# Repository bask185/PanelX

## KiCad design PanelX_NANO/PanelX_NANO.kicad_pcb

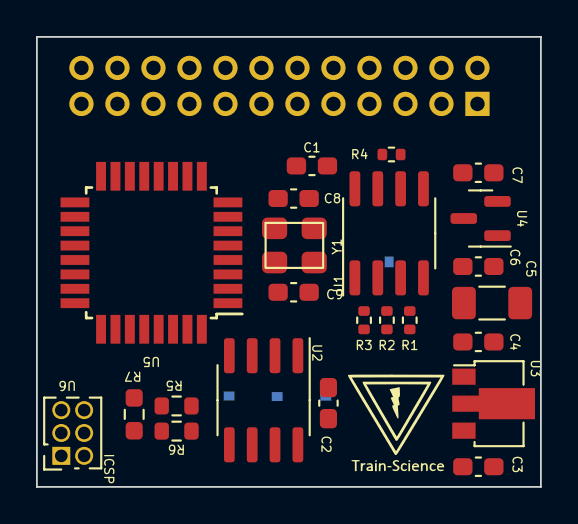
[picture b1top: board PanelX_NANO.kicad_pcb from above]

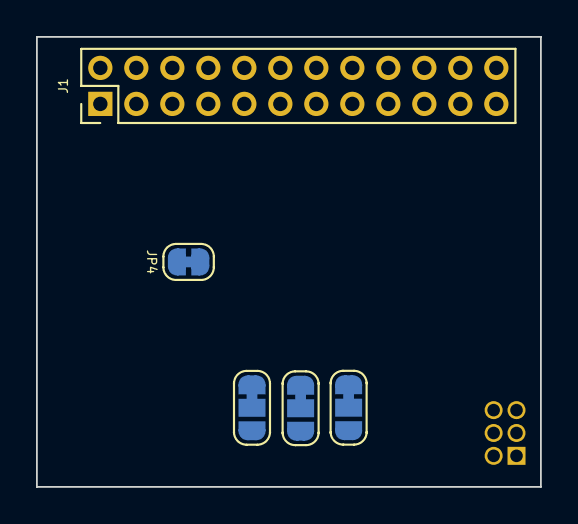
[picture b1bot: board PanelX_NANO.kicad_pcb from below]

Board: 2 copper layers, 28.0 x 25.0 mm, 28 parts (5 on the bottom side), 33 nets, no tracks yet.

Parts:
C1: 100n; C_0603_1608Metric_Pad1.08x0.95mm_HandSolder
C2, C4: 100nF; C_0603_1608Metric_Pad1.08x0.95mm_HandSolder
C3: 330nF; C_0603_1608Metric_Pad1.08x0.95mm_HandSolder
C5: 100uF; C_1206_3216Metric_Pad1.33x1.80mm_HandSolder
C6, C7: 1uF; C_0603_1608Metric_Pad1.08x0.95mm_HandSolder
C8, C9: 12pF; C_0603_1608Metric_Pad1.08x0.95mm_HandSolder
J1: Conn_02x12_Counter_Clockwise; PinHeader_2x12_P2.00mm_Vertical
JP1, JP2, JP3: SolderJumper_3_Bridged12; SolderJumper-3_P1.3mm_Bridged12_RoundedPad1.0x1.5mm_NumberL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
JP4: SolderJumper_2_Bridged; SolderJumper-2_P1.3mm_Bridged_RoundedPad1.0x1.5mm
R1, R2, R3: 10k; R_0402_1005Metric
R4: 120R; R_0402_1005Metric
R5, R6: 4k7; R_0603_1608Metric
R7: 10k; R_0603_1608Metric_Pad0.98x0.95mm_HandSolder
U1: MAX485E; SOIC-8_3.9x4.9mm_P1.27mm
U2: 24LC256; SOIC-8_3.9x4.9mm_P1.27mm
U3: L78L05_SOT89; SOT-89-3
U4: XC6206PxxxMR; SOT-23
U5: ATmega328-A; TQFP-32_7x7mm_P0.8mm
U6: HEADER_3x2; PinSocket_2x03_P1.27mm_Vertical
Y1: crystal_arduino

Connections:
+3V3: C7.1, J1.1, U4.2 (VO)
+5V: C1.1, C2.2, C4.1, C5.1, C6.1, J1.2, JP1.3 (B), JP2.3 (B), JP3.3 (B), R1.1, R2.1, R3.1, R5.1, R6.1, R7.1, U1.8 (VCC), U2.8 (VCC), U3.1 (OUT), U4.3 (VI), U5.4 (VCC), U5.6 (VCC), U5.18 (AVCC), U6.5
+12V: C3.1, J1.4, U3.3 (IN)
/EEPROM/A0: JP1.2 (C), U2.1 (A0)
/EEPROM/A1: JP2.2 (C), U2.2 (A1)
/EEPROM/A2: JP3.2 (C), U2.3 (A2)
/atmega328/RESET: R7.2, U5.29 (~RESET/PC6), U6.2
/atmega328/X1: C9.2, U5.7 (XTAL1/PB6), Y1.1
/atmega328/X2: C8.2, U5.8 (XTAL2/PB7), Y1.3
A: J1.6, R4.2, U1.6 (A)
B: J1.8, JP4.2 (B), U1.7 (B)
GND: C1.2, C2.1, C3.2, C4.2, C5.2, C6.2, C7.2, C8.1, C9.1, J1.10, JP1.1 (A), JP2.1 (A), JP3.1 (A), U1.5 (GND), U2.4 (GND), U2.7 (WP), U3.2 (GND), U4.1 (GND), U5.3 (GND), U5.5 (GND), U5.21 (GND), U6.1, Y1.2 (GND), Y1.4 (GND)
GPIO1: J1.3, U5.1 (PD3)
GPIO2: J1.5, U5.2 (PD4)
GPIO3: J1.7, U5.9 (PD5)
GPIO4: J1.9, U5.10 (PD6)
GPIO5: J1.11, U5.11 (PD7)
GPIO6: J1.13, U5.12 (PB0)
GPIO7: J1.15, U5.13 (PB1)
GPIO8: J1.17, U5.14 (PB2)
GPIO9: J1.19, U5.15 (PB3), U6.3
GPIO10: J1.21, U5.16 (PB4), U6.6
GPIO11: J1.23, U5.17 (PB5), U6.4
GPIO12: J1.24, U5.23 (PC0)
GPIO13: J1.22, U5.24 (PC1)
GPIO14: J1.20, U5.25 (PC2)
GPIO15: J1.18, U5.26 (PC3)
unnamed: JP4.1 (A), R4.1
Rx: R3.2, U1.1 (RO), U5.30 (PD0)
SCL: R6.2, U2.6 (SCL), U5.28 (PC5)
SDA: R5.2, U2.5 (SDA), U5.27 (PC4)
Tx: R1.2, U1.4 (DI), U5.31 (PD1)
dir: R2.2, U1.2 (~RE), U1.3 (DE), U5.32 (PD2)

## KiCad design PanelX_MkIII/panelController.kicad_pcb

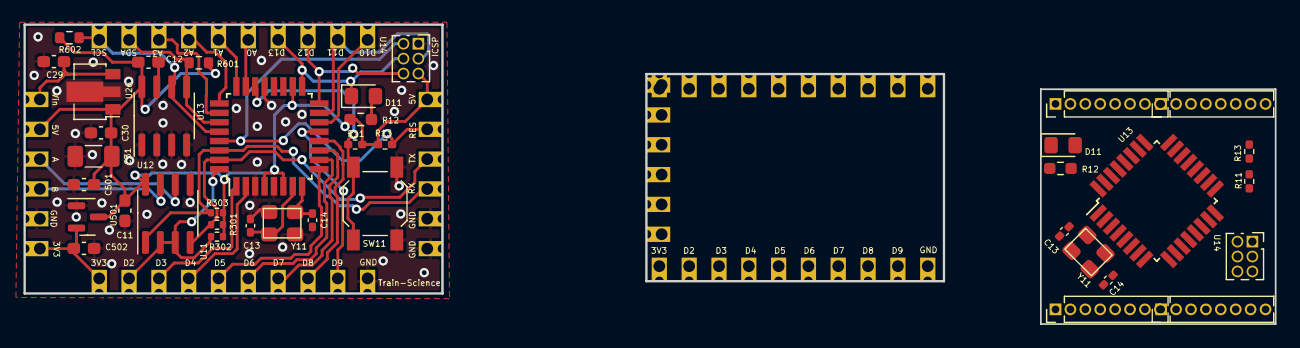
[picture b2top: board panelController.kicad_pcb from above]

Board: 2 copper layers, 106.5 x 25.5 mm, 42 parts (0 on the bottom side), 31 nets.

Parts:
C11: 100n; C_0603_1608Metric_Pad1.08x0.95mm_HandSolder
C12, C30: 100nF; C_0603_1608Metric_Pad1.08x0.95mm_HandSolder
C13, C13#2, C14, C14#2: 12pF; C_0402_1005Metric_Pad0.74x0.62mm_HandSolder
C29: 330nF; C_0603_1608Metric_Pad1.08x0.95mm_HandSolder
C31: 100uF; C_1206_3216Metric_Pad1.33x1.80mm_HandSolder
C501, C502: 1uF; C_0603_1608Metric_Pad1.08x0.95mm_HandSolder
D11, D11#2: LED; LED_0805_2012Metric_Pad1.15x1.40mm_HandSolder
J11, J11#2, J12: Conn_01x05_Male; castellated_2.54mm_01x06
J401, J401#2, J403, J403#2: Conn_01x10_Male; castellated_2.54mm_01x10
R11, R11#2, R13, R13#2: 10k; R_0402_1005Metric_Pad0.72x0.64mm_HandSolder
R12, R12#2: 6k2; R_0603_1608Metric_Pad0.98x0.95mm_HandSolder
R301, R302, R303: 10k; R_0402_1005Metric
R601, R602: 4k7; R_0603_1608Metric
SW11: SW_SPST; SW_SPST_SKQG_WithStem
U11: MAX485E; SOIC-8_3.9x4.9mm_P1.27mm
U12: 24LC256; SOIC-8_3.9x4.9mm_P1.27mm
U13, U13#2: ATmega328-A; TQFP-32_7x7mm_P0.8mm
U14, U14#2: HEADER_3x2; PinSocket_2x03_P1.27mm_Vertical
U26: L78L05_SOT89; SOT-89-3
U501: XC6206PxxxMR; SOT-23
Y11, Y11#2: crystal_arduino

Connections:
+3V3: C502.1, J11.6, J11#2.6, J401.1, J401#2.1, U501.2 (VO)
+5V: C11.1, C12.2, C30.1, C31.1, C501.1, J11.2, J11#2.2, J12.6, R11.1, R11#2.1, R12.1, R12#2.1, R13.1, R13#2.1, R301.1, R302.1, R303.1, R601.1, R602.1, U11.8 (VCC), U12.8 (VCC), U13.4 (VCC), U13.6 (VCC), U13.18 (AVCC), U13#2.4 (VCC), U13#2.6 (VCC), U13#2.18 (AVCC), U14.5, U14#2.5, U26.1 (OUT), U501.3 (VI)
+12V: C29.1, J11.1, J11#2.1, U26.3 (IN)
/atmega328/X1: C13.2, C13#2.2, U13.7 (XTAL1/PB6), U13#2.7 (XTAL1/PB6), Y11.1, Y11#2.1
/atmega328/X2: C14.2, C14#2.2, U13.8 (XTAL2/PB7), U13#2.8 (XTAL2/PB7), Y11.3, Y11#2.3
A: J11.3, J11#2.3, U11.6 (A)
B: J11.4, J11#2.4, U11.7 (B)
GND: C11.2, C12.1, C13.1, C13#2.1, C14.1, C14#2.1, C29.2, C30.2, C31.2, C501.2, C502.2, J11.5, J11#2.5, J12.1, J12.2, J401.10, J401#2.10, SW11.1 (A), U11.5 (GND), U12.1 (A0), U12.2 (A1), U12.3 (A2), U12.4 (GND), U12.7 (WP), U13.3 (GND), U13.5 (GND), U13.21 (GND), U13#2.3 (GND), U13#2.5 (GND), U13#2.21 (GND), U14.1, U14#2.1, U26.2 (GND), U501.1 (GND), Y11.2 (GND), Y11.4 (GND), Y11#2.2 (GND), Y11#2.4 (GND)
GPIO2: J401.2, J401#2.2, R302.2, U11.2 (~RE), U11.3 (DE), U13.32 (PD2), U13#2.32 (PD2)
GPIO3: J401.3, J401#2.3, U13.1 (PD3), U13#2.1 (PD3)
GPIO4: J401.4, J401#2.4, U13.2 (PD4), U13#2.2 (PD4)
GPIO5: J401.5, J401#2.5, U13.9 (PD5), U13#2.9 (PD5)
GPIO6: J401.6, J401#2.6, U13.10 (PD6), U13#2.10 (PD6)
GPIO7: J401.7, J401#2.7, U13.11 (PD7), U13#2.11 (PD7)
GPIO8: J401.8, J401#2.8, U13.12 (PB0), U13#2.12 (PB0)
GPIO9: J401.9, J401#2.9, U13.13 (PB1), U13#2.13 (PB1)
GPIO10: J403.1, J403#2.1, U13.14 (PB2), U13#2.14 (PB2)
GPIO11: J403.2, J403#2.2, U13.15 (PB3), U13#2.15 (PB3), U14.3, U14#2.3
GPIO12: J403.3, J403#2.3, U13.16 (PB4), U13#2.16 (PB4), U14.6, U14#2.6
GPIO13: D11.1 (K), D11#2.1 (K), J403.4, J403#2.4, U13.17 (PB5), U13#2.17 (PB5), U14.4, U14#2.4
GPIO_A0: J403.5, J403#2.5, U13.23 (PC0), U13#2.23 (PC0)
GPIO_A1: J403.6, J403#2.6, U13.24 (PC1), U13#2.24 (PC1)
GPIO_A2: J403.7, J403#2.7, U13.25 (PC2), U13#2.25 (PC2)
GPIO_A3: J403.8, J403#2.8, U13.26 (PC3), U13#2.26 (PC3)
unnamed: D11.2 (A), D11#2.2 (A), R12.2, R12#2.2
unnamed: R11.2, R11#2.2, SW11.2 (B), U13.22 (ADC7), U13#2.22 (ADC7)
RESET: J12.5, R13.2, R13#2.2, U13.29 (~RESET/PC6), U13#2.29 (~RESET/PC6), U14.2, U14#2.2
Rx: J12.3, R303.2, U11.1 (RO), U13.30 (PD0), U13#2.30 (PD0)
SCL: J403.10, J403#2.10, R602.2, U12.6 (SCL), U13.28 (PC5), U13#2.28 (PC5)
SDA: J403.9, J403#2.9, R601.2, U12.5 (SDA), U13.27 (PC4), U13#2.27 (PC4)
Tx: J12.4, R301.2, U11.4 (DI), U13.31 (PD1), U13#2.31 (PD1)

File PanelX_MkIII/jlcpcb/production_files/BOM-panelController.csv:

Comment,Designator,Footprint,LCSC
crystal_arduino,Y11,crystal_arduino,C13738
100nF,"C12,C30",C_0603_1608Metric_Pad1.08x0.95mm_HandSolder,C14663
ATmega328-A,U13,TQFP-32_7x7mm_P0.8mm,C14877
100uF,C31,C_1206_3216Metric_Pad1.33x1.80mm_HandSolder,C15008
12pF,"C13,C14",C_0402_1005Metric_Pad0.74x0.62mm_HandSolder,C1547
1uF,"C501,C502",C_0603_1608Metric_Pad1.08x0.95mm_HandSolder,C15849
330nF,C29,C_0603_1608Metric_Pad1.08x0.95mm_HandSolder,C1615
10k,"R301,R302,R303",R_0402_1005Metric,C17414
LED,D11,LED_0805_2012Metric_Pad1.15x1.40mm_HandSolder,C2296
4k7,"R601,R602",R_0603_1608Metric,C23162
10k,"R11,R13",R_0402_1005Metric_Pad0.72x0.64mm_HandSolder,C25744
24LC256,U12,SOIC-8_3.9x4.9mm_P1.27mm,C2987263
SW_SPST,SW11,SW_SPST_SKQG_WithStem,C318884
6k2,R12,R_0603_1608Metric_Pad0.98x0.95mm_HandSolder,C4260
XC6206PxxxMR,U501,SOT-23,C5446
MAX485E,U11,SOIC-8_3.9x4.9mm_P1.27mm,C668206
L78L05_SOT89,U26,SOT-89-3,C71136
Conn_01x10_Male,J401,castellated_2.54mm_01x10,
100n,C11,C_0603_1608Metric_Pad1.08x0.95mm_HandSolder,
Conn_01x10_Male,J403,castellated_2.54mm_01x10,
HEADER_3x2,U14,PinSocket_2x03_P1.27mm_Vertical,
Conn_01x05_Male,J12,castellated_2.54mm_01x06,
Conn_01x05_Male,J11,castellated_2.54mm_01x06,

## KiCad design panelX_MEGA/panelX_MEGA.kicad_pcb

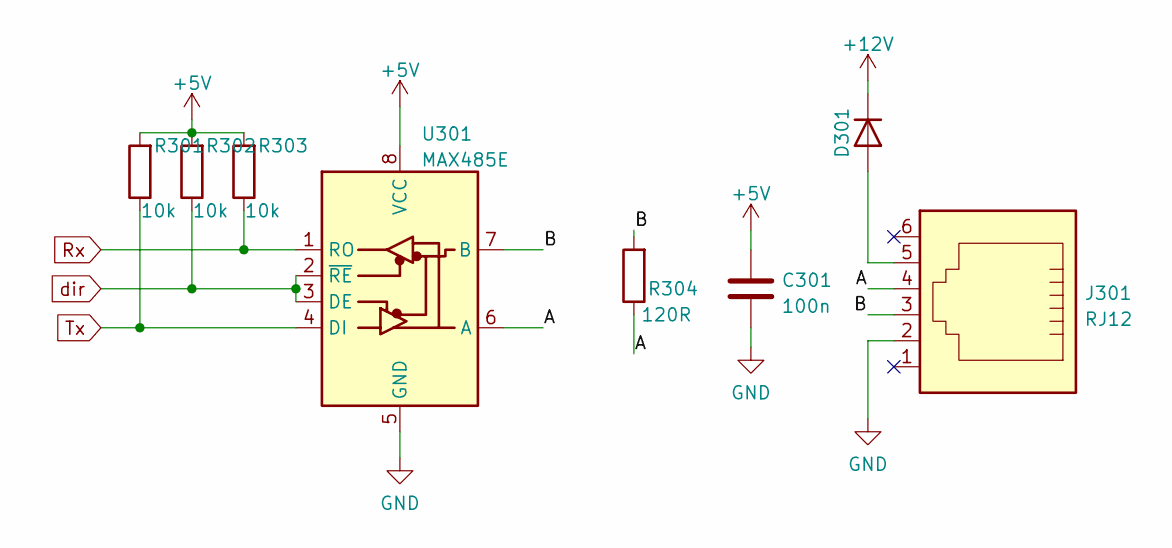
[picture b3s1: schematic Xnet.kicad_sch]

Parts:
C301: 100n
D301: D; D_SMA; JLCPCB Part# C14996
J301: RJ12
R301, R302, R303: 10k; R_0805_2012Metric_Pad1.20x1.40mm_HandSolder
R304: 120R
U301: MAX485E

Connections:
+5V: C301.1, R301.2, R302.2, R303.2, U301.8 (VCC); also elsewhere on the board
+12V: D301.1 (K); also elsewhere on the board
/Xnet/A: J301.4, R304.1, U301.6 (A)
/Xnet/B: J301.3, R304.2, U301.7 (B)
GND: C301.2, J301.2, U301.5 (GND); also elsewhere on the board
unnamed: D301.2 (A), J301.5
Rx: R303.1, U301.1 (RO); also elsewhere on the board
Tx: R301.1, U301.4 (DI); also elsewhere on the board
dir: R302.1, U301.2 (~RE), U301.3 (DE); also elsewhere on the board

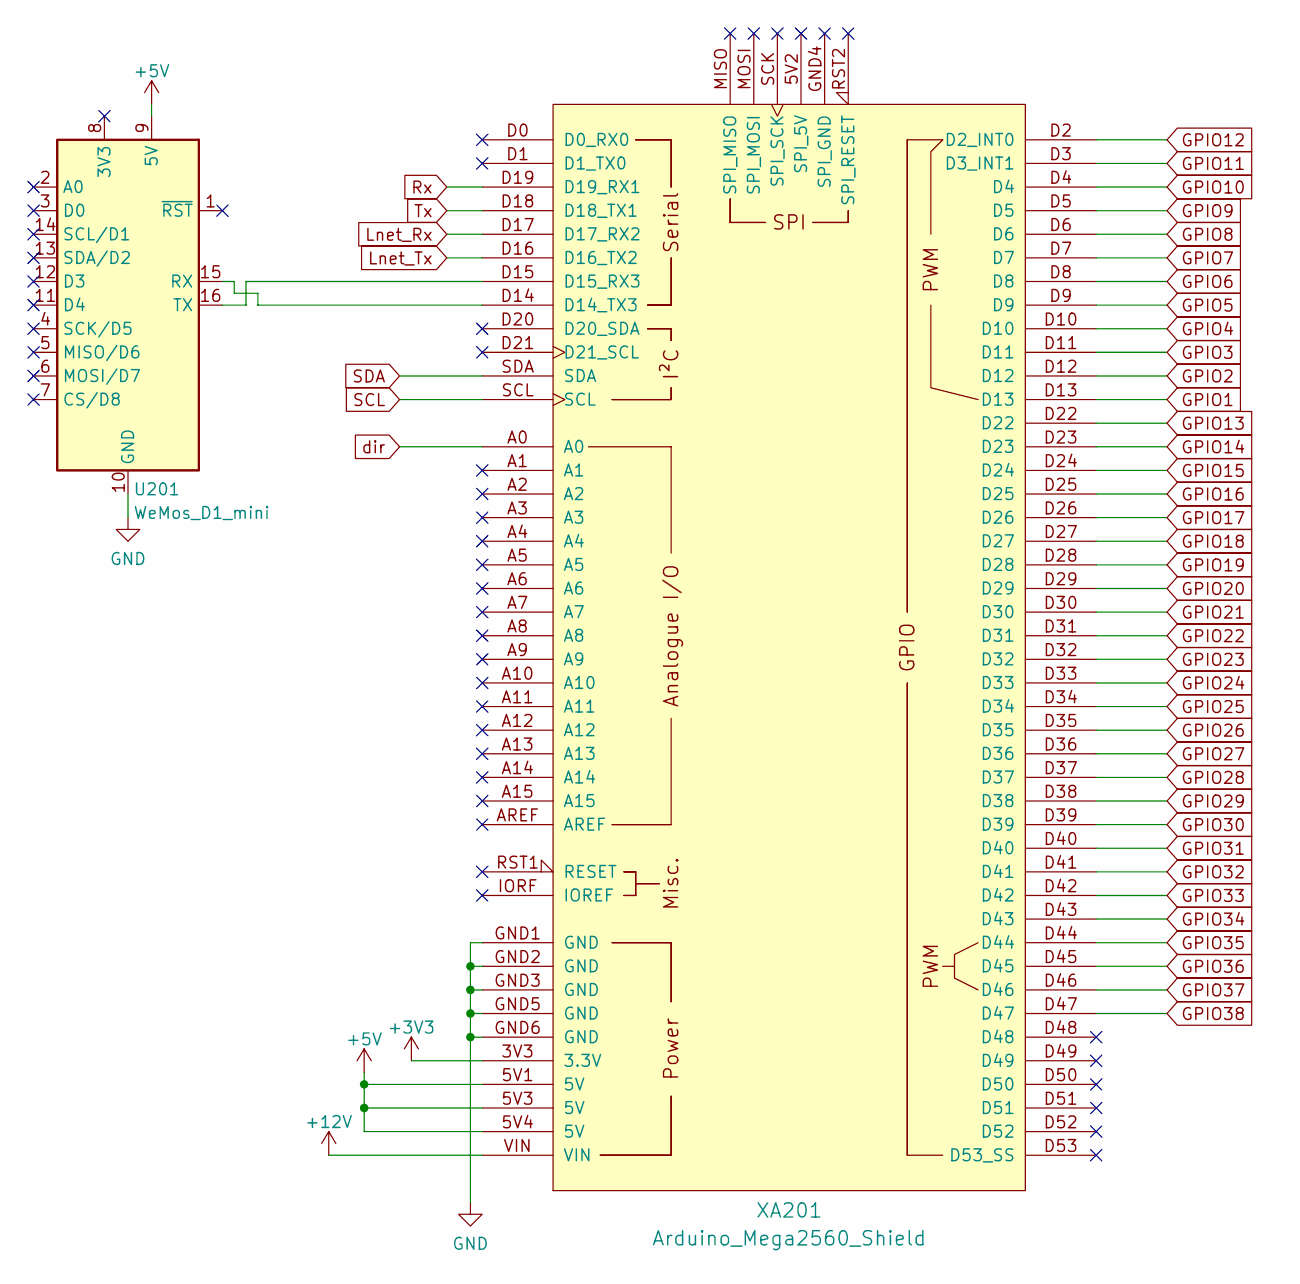
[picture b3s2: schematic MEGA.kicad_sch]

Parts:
U201: WeMos_D1_mini; WEMOS_D1_mini_light
XA201: Arduino_Mega2560_Shield

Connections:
+3V3: XA201.3V3 (3.3V); also elsewhere on the board
+5V: U201.9 (5V), XA201.5V1 (5V), XA201.5V3 (5V), XA201.5V4 (5V); also elsewhere on the board
+12V: XA201.VIN; also elsewhere on the board
GND: U201.10 (GND), XA201.GND1 (GND), XA201.GND2 (GND), XA201.GND3 (GND), XA201.GND5 (GND), XA201.GND6 (GND); also elsewhere on the board
GPIO1: XA201.D13; also elsewhere on the board
GPIO2: XA201.D12; also elsewhere on the board
GPIO3: XA201.D11; also elsewhere on the board
GPIO4: XA201.D10; also elsewhere on the board
GPIO5: XA201.D9; also elsewhere on the board
GPIO6: XA201.D8; also elsewhere on the board
GPIO7: XA201.D7; also elsewhere on the board
GPIO8: XA201.D6; also elsewhere on the board
GPIO9: XA201.D5; also elsewhere on the board
GPIO10: XA201.D4; also elsewhere on the board
GPIO11: XA201.D3 (D3_INT1); also elsewhere on the board
GPIO12: XA201.D2 (D2_INT0); also elsewhere on the board
GPIO13: XA201.D22; also elsewhere on the board
GPIO14: XA201.D23; also elsewhere on the board
GPIO15: XA201.D24; also elsewhere on the board
GPIO16: XA201.D25; also elsewhere on the board
GPIO17: XA201.D26; also elsewhere on the board
GPIO18: XA201.D27; also elsewhere on the board
GPIO19: XA201.D28; also elsewhere on the board
GPIO20: XA201.D29; also elsewhere on the board
GPIO21: XA201.D30; also elsewhere on the board
GPIO22: XA201.D31; also elsewhere on the board
GPIO23: XA201.D32; also elsewhere on the board
GPIO24: XA201.D33; also elsewhere on the board
GPIO25: XA201.D34; also elsewhere on the board
GPIO26: XA201.D35; also elsewhere on the board
GPIO27: XA201.D36; also elsewhere on the board
GPIO28: XA201.D37; also elsewhere on the board
GPIO29: XA201.D38; also elsewhere on the board
GPIO30: XA201.D39; also elsewhere on the board
GPIO31: XA201.D40; also elsewhere on the board
GPIO32: XA201.D41; also elsewhere on the board
GPIO33: XA201.D42; also elsewhere on the board
GPIO34: XA201.D43; also elsewhere on the board
GPIO35: XA201.D44; also elsewhere on the board
GPIO36: XA201.D45; also elsewhere on the board
GPIO37: XA201.D46; also elsewhere on the board
GPIO38: XA201.D47; also elsewhere on the board
Lnet_Rx: XA201.D17 (D17_RX2); also elsewhere on the board
Lnet_Tx: XA201.D16 (D16_TX2); also elsewhere on the board
unnamed: U201.15 (RX), XA201.D14 (D14_TX3)
unnamed: U201.16 (TX), XA201.D15 (D15_RX3)
Rx: XA201.D19 (D19_RX1); also elsewhere on the board
SCL: XA201.SCL; also elsewhere on the board
SDA: XA201.SDA; also elsewhere on the board
Tx: XA201.D18 (D18_TX1); also elsewhere on the board
dir: XA201.A0; also elsewhere on the board

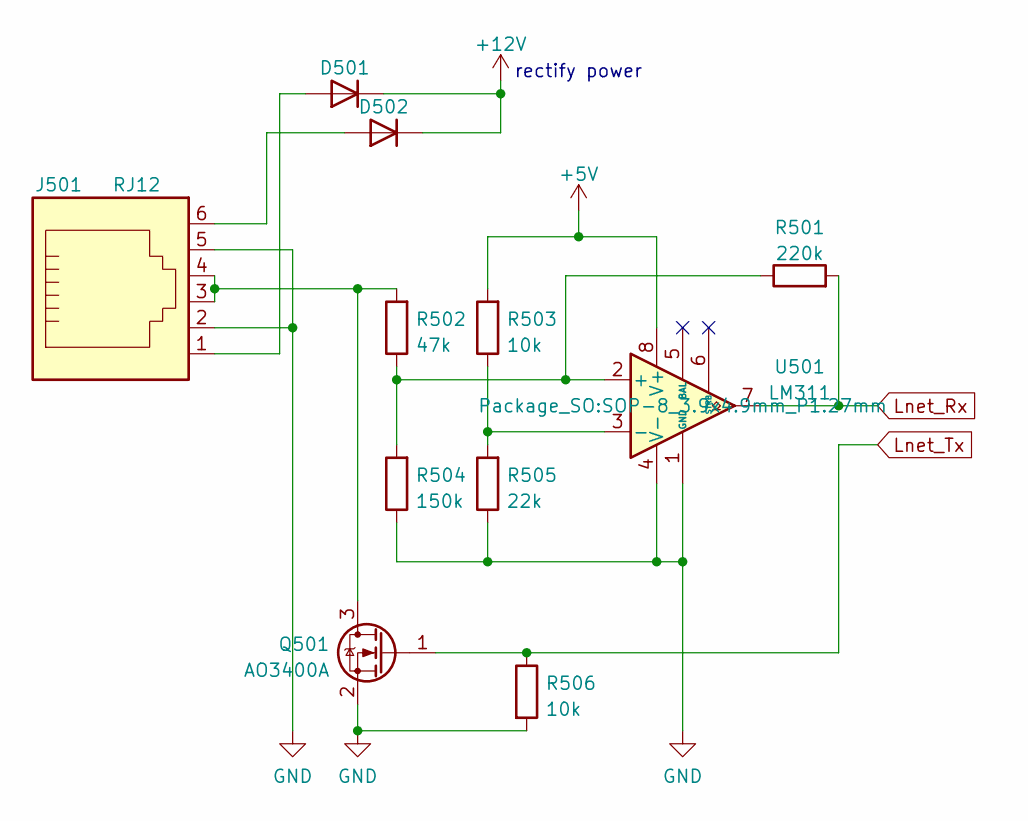
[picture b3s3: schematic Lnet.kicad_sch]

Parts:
D501, D502: D; D_SMA; JLCPCB Part# C14996
J501: RJ12; RJ12_Amphenol_54601; JLCPCB Part# C77859
Q501: AO3400A; SOT-23; JLCPCB Part# C20917
R501: 220k; R_0805_2012Metric_Pad1.20x1.40mm_HandSolder
R502: 47k; R_0805_2012Metric_Pad1.20x1.40mm_HandSolder
R503, R506: 10k; R_0805_2012Metric_Pad1.20x1.40mm_HandSolder
R504: 150k; R_0805_2012Metric_Pad1.20x1.40mm_HandSolder
R505: 22k; R_0805_2012Metric_Pad1.20x1.40mm_HandSolder
U501: LM311; SOP-8_3.9x4.9mm_P1.27mm; JLCPCB Part# C434495

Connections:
+5V: R503.2, U501.8 (V+); also elsewhere on the board
+12V: D501.1 (K), D502.1 (K); also elsewhere on the board
GND: J501.2, J501.5, Q501.2 (S), R504.1, R505.1, R506.2, U501.1 (GND), U501.4 (V-); also elsewhere on the board
Lnet_Rx: R501.2, U501.7; also elsewhere on the board
Lnet_Tx: Q501.1 (G), R506.1; also elsewhere on the board
unnamed: D501.2 (A), J501.1
unnamed: D502.2 (A), J501.6
unnamed: J501.3, J501.4, Q501.3 (D), R502.2
unnamed: R501.1, R502.1, R504.2, U501.2 (+)
unnamed: R503.1, R505.2, U501.3 (-)

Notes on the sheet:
rectify power

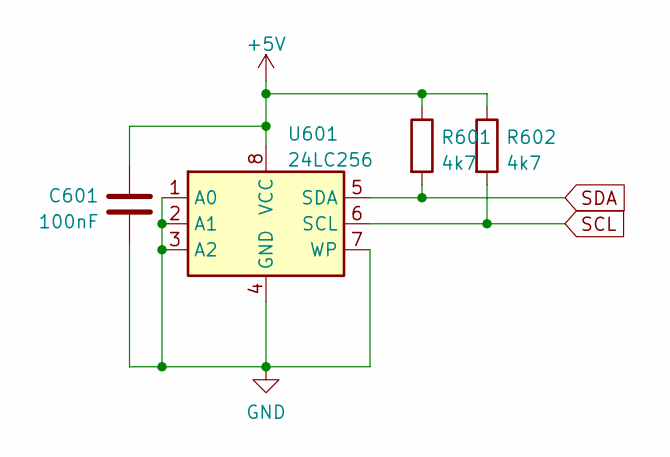
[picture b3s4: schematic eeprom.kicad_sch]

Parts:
C601: 100nF; C_0603_1608Metric_Pad1.08x0.95mm_HandSolder; JLCPCB Part# C14663
R601, R602: 4k7; R_0603_1608Metric; JLCPCB Part# C23162
U601: 24LC256; SOIC-8_3.9x4.9mm_P1.27mm; JLCPCB Part# C2987263

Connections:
+5V: C601.2, R601.1, R602.1, U601.8 (VCC); also elsewhere on the board
GND: C601.1, U601.1 (A0), U601.2 (A1), U601.3 (A2), U601.4 (GND), U601.7 (WP); also elsewhere on the board
SCL: R602.2, U601.6 (SCL); also elsewhere on the board
SDA: R601.2, U601.5 (SDA); also elsewhere on the board

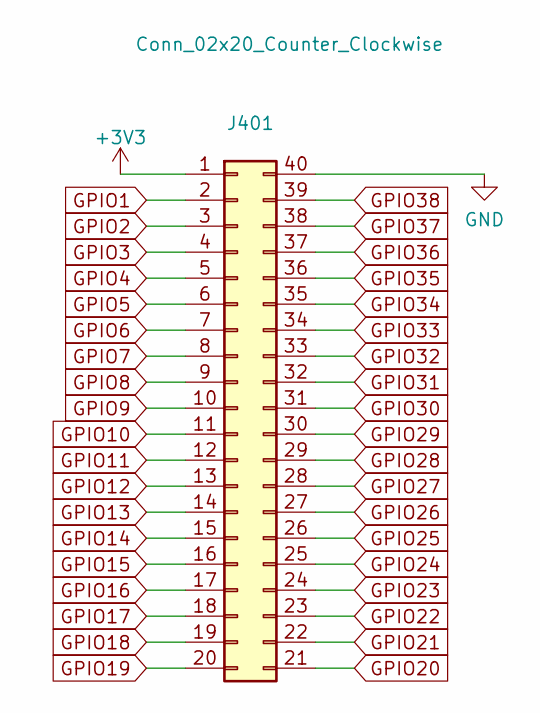
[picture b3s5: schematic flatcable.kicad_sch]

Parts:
J401: Conn_02x20_Counter_Clockwise

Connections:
+3V3: J401.1; also elsewhere on the board
GND: J401.40; also elsewhere on the board
GPIO1: J401.2; also elsewhere on the board
GPIO2: J401.3; also elsewhere on the board
GPIO3: J401.4; also elsewhere on the board
GPIO4: J401.5; also elsewhere on the board
GPIO5: J401.6; also elsewhere on the board
GPIO6: J401.7; also elsewhere on the board
GPIO7: J401.8; also elsewhere on the board
GPIO8: J401.9; also elsewhere on the board
GPIO9: J401.10; also elsewhere on the board
GPIO10: J401.11; also elsewhere on the board
GPIO11: J401.12; also elsewhere on the board
GPIO12: J401.13; also elsewhere on the board
GPIO13: J401.14; also elsewhere on the board
GPIO14: J401.15; also elsewhere on the board
GPIO15: J401.16; also elsewhere on the board
GPIO16: J401.17; also elsewhere on the board
GPIO17: J401.18; also elsewhere on the board
GPIO18: J401.19; also elsewhere on the board
GPIO19: J401.20; also elsewhere on the board
GPIO20: J401.21; also elsewhere on the board
GPIO21: J401.22; also elsewhere on the board
GPIO22: J401.23; also elsewhere on the board
GPIO23: J401.24; also elsewhere on the board
GPIO24: J401.25; also elsewhere on the board
GPIO25: J401.26; also elsewhere on the board
GPIO26: J401.27; also elsewhere on the board
GPIO27: J401.28; also elsewhere on the board
GPIO28: J401.29; also elsewhere on the board
GPIO29: J401.30; also elsewhere on the board
GPIO30: J401.31; also elsewhere on the board
GPIO31: J401.32; also elsewhere on the board
GPIO32: J401.33; also elsewhere on the board
GPIO33: J401.34; also elsewhere on the board
GPIO34: J401.35; also elsewhere on the board
GPIO35: J401.36; also elsewhere on the board
GPIO36: J401.37; also elsewhere on the board
GPIO37: J401.38; also elsewhere on the board
GPIO38: J401.39; also elsewhere on the board

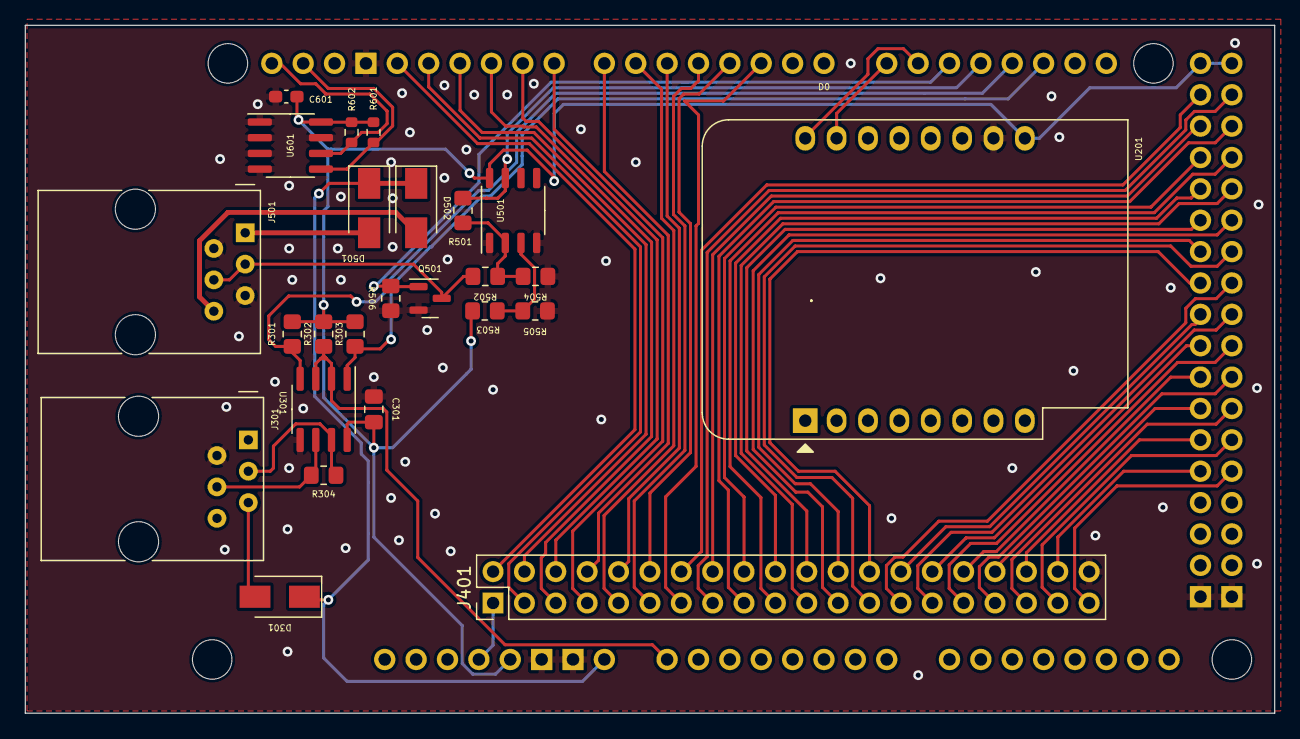
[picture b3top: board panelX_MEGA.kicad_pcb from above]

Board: 2 copper layers, 101.1 x 55.7 mm, 26 parts (0 on the bottom side), 59 nets.

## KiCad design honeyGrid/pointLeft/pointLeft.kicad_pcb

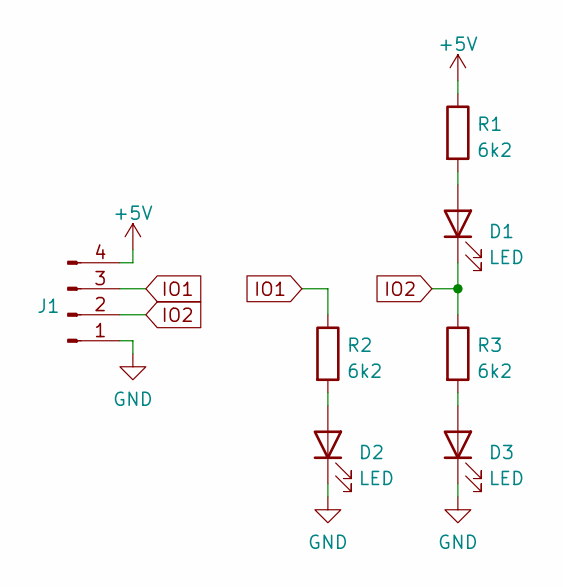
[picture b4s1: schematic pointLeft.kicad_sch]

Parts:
D1, D2, D3: LED; LED_0805_2012Metric_Pad1.15x1.40mm_HandSolder; JLCPCB Part# C2296
J1: Conn_01x04_Male; JST_PH_B4B-PH-SM4-TB_1x04-1MP_P2.00mm_Vertical
R1, R2, R3: 6k2; R_0603_1608Metric_Pad0.98x0.95mm_HandSolder; JLCPCB Part# C4260

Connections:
+5V: J1.4, R1.1
GND: D2.1 (K), D3.1 (K), J1.1
IO1: J1.3, R2.1
IO2: D1.1 (K), J1.2, R3.1
unnamed: D1.2 (A), R1.2
unnamed: D2.2 (A), R2.2
unnamed: D3.2 (A), R3.2

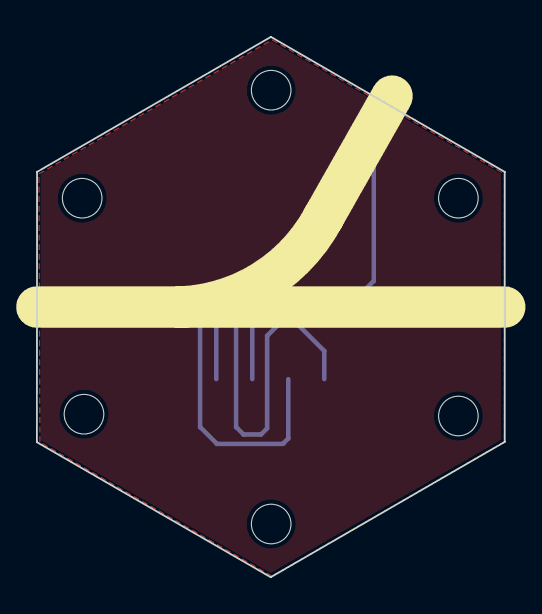
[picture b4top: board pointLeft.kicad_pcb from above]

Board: 2 copper layers, 26.0 x 30.0 mm, 7 parts (1 on the bottom side), 7 nets.

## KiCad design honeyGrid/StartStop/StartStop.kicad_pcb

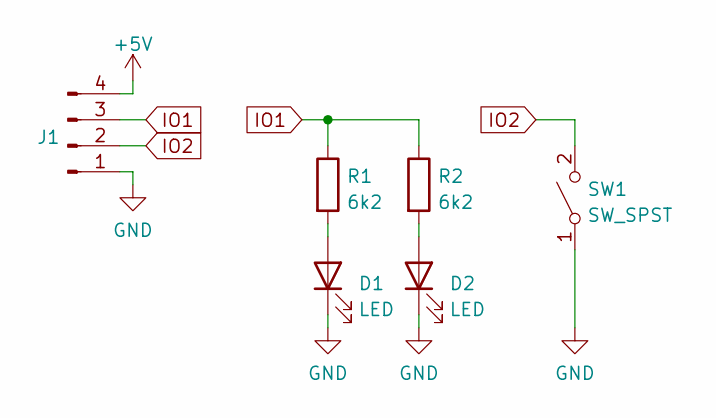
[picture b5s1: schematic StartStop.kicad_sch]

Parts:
D1, D2: LED; LED_0805_2012Metric_Pad1.15x1.40mm_HandSolder; JLCPCB Part# C2296
J1: (no value)
R1, R2: 6k2; R_0603_1608Metric_Pad0.98x0.95mm_HandSolder; JLCPCB Part# C4260
SW1: SW_SPST; SW_PUSH_6mm_H7.3mm

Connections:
+5V: J1.4
GND: D1.1 (K), D2.1 (K), J1.1, SW1.1 (A)
IO1: J1.3, R1.1, R2.1
IO2: J1.2, SW1.2 (B)
unnamed: D1.2 (A), R1.2
unnamed: D2.2 (A), R2.2

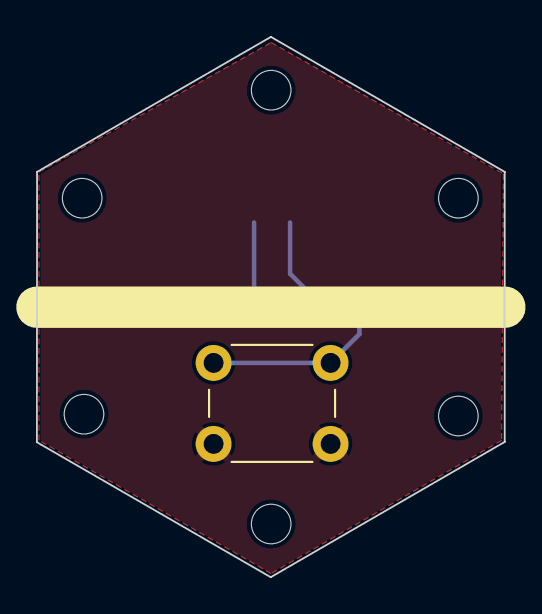
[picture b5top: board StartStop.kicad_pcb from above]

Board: 2 copper layers, 26.0 x 30.0 mm, 6 parts (1 on the bottom side), 5 nets.

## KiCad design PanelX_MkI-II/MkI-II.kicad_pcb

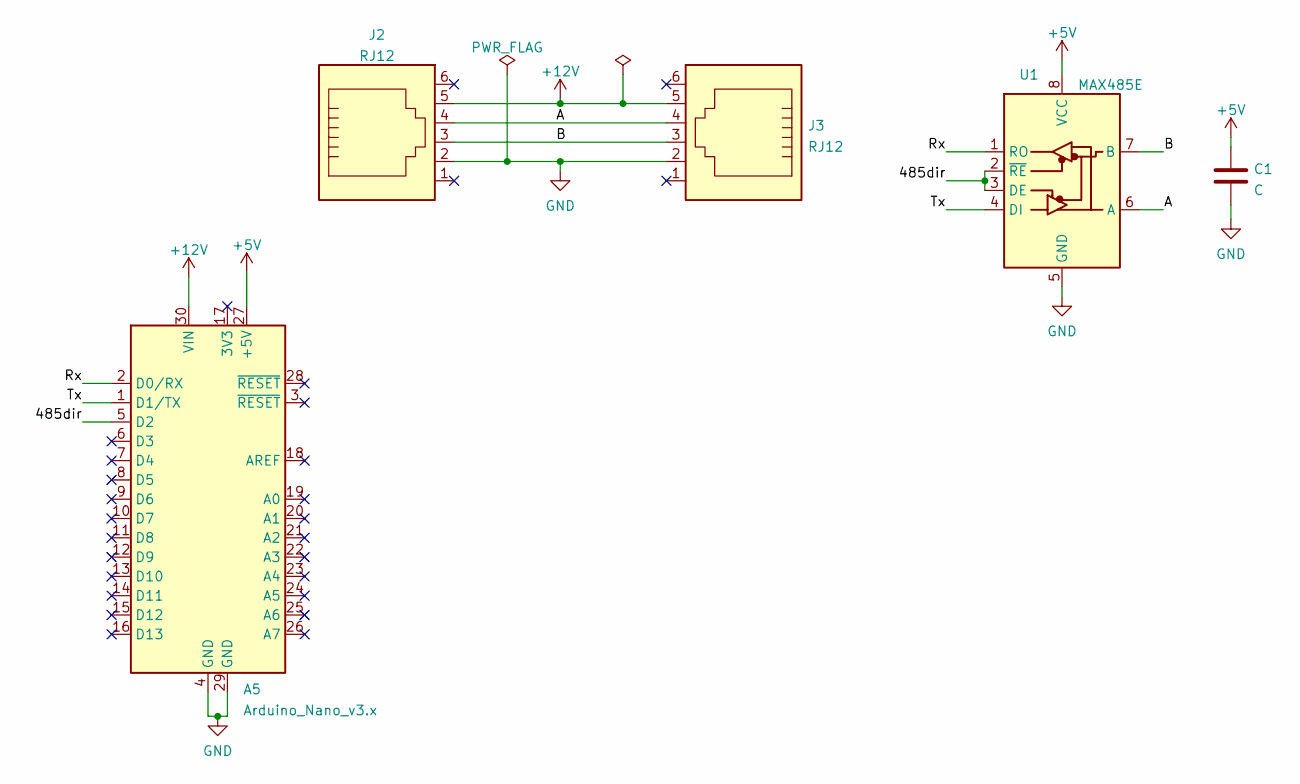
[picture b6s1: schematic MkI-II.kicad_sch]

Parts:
A5: Arduino_Nano_v3.x; Arduino_Nano
C1: C; C_Disc_D3.0mm_W1.6mm_P2.50mm
J2, J3: RJ12; RJ12_Amphenol_54601
U1: MAX485E; DIP-8_W7.62mm

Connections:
+5V: A5.27 (+5V), C1.1, U1.8 (VCC)
+12V: A5.30 (VIN), J2.5, J3.5
/485dir: A5.5 (D2), U1.2 (~RE), U1.3 (DE)
/A: J2.4, J3.4, U1.6 (A)
/B: J2.3, J3.3, U1.7 (B)
/Rx: A5.2 (D0/RX), U1.1 (RO)
/Tx: A5.1 (D1/TX), U1.4 (DI)
GND: A5.4 (GND), A5.29 (GND), C1.2, J2.2, J3.2, U1.5 (GND)

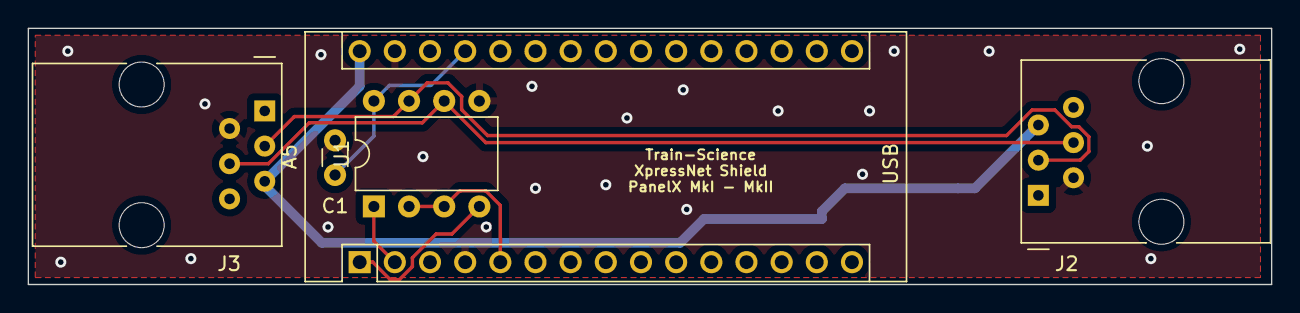
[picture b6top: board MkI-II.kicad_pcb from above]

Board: 2 copper layers, 89.8 x 18.5 mm, 5 parts (0 on the bottom side), 8 nets.

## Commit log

2023-02-01 added nano project to repo. Must be modular flatcable design. I want to make 2 versions, one with voltage regulator and Xnet and one as I2C slave
2023-02-02 Deleted zip files from repo
2023-02-02 I picked a suitable connector. I will use plain 2x12 female n male connectors for the b2b connector. Death to flatcables! The RJ12 connector still goed on the panel carrier board. I will look for ver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
2023-02-02 renamed the NANO to controller. Routing is finished DRC is check. The schematic must be checked as well
